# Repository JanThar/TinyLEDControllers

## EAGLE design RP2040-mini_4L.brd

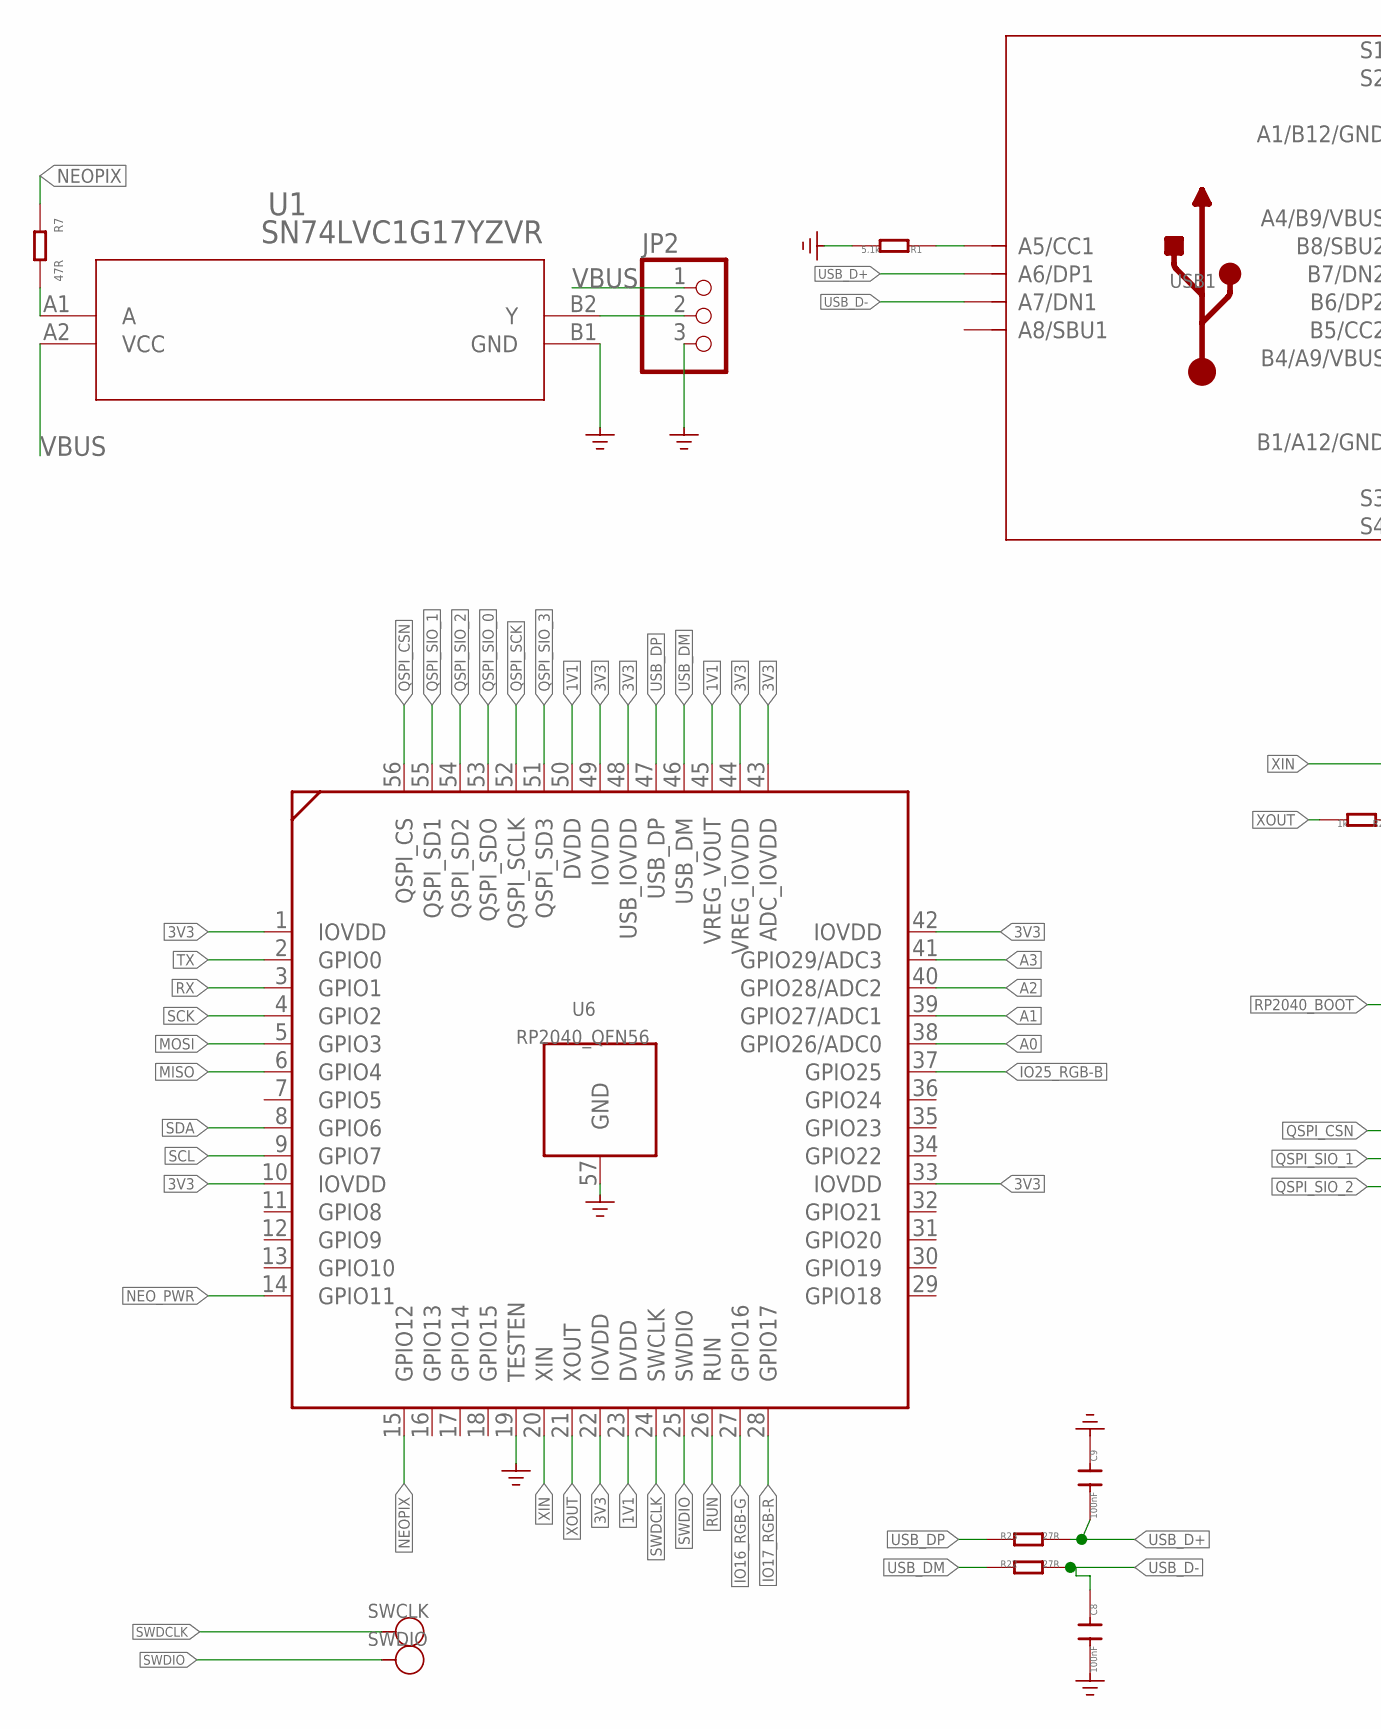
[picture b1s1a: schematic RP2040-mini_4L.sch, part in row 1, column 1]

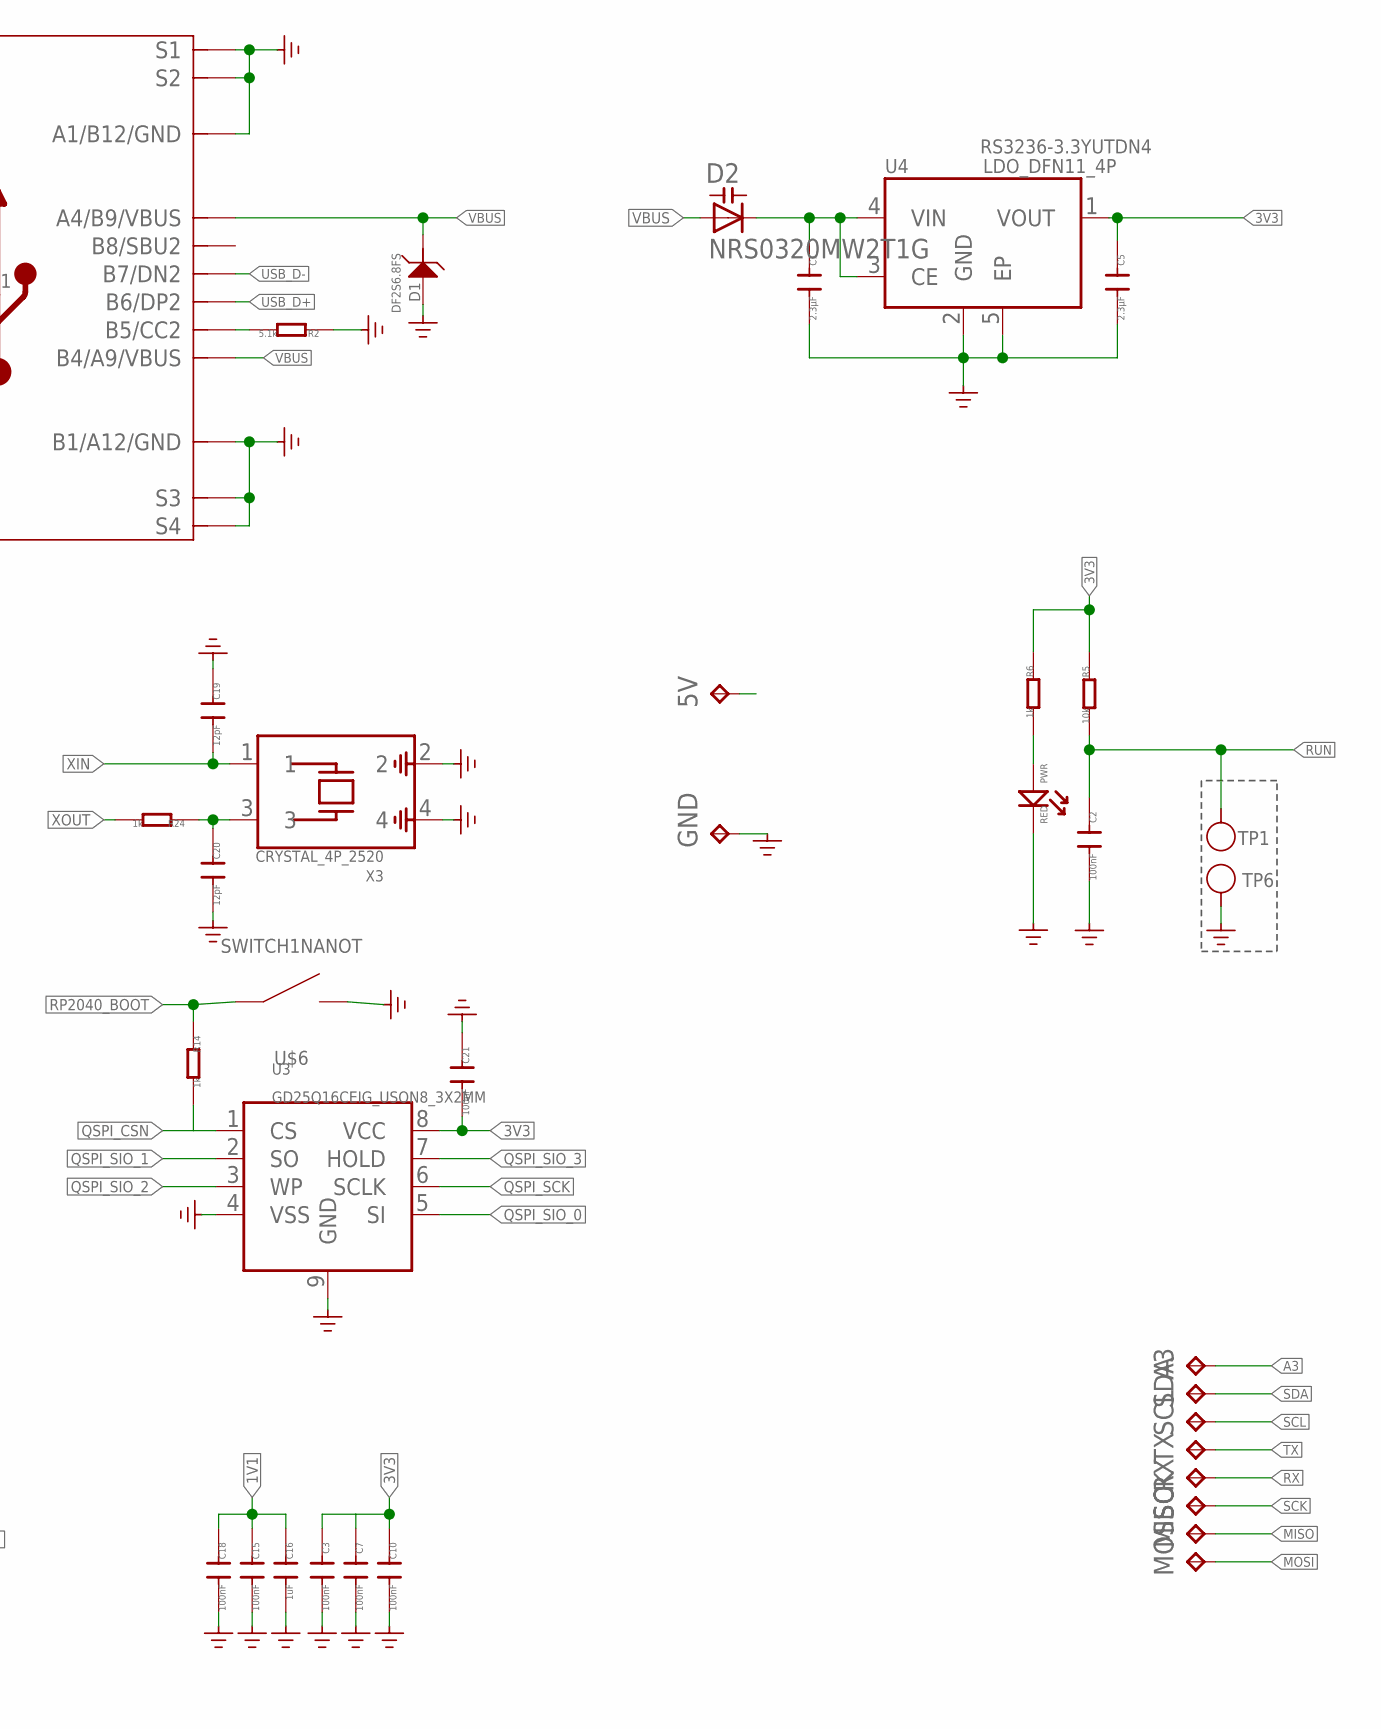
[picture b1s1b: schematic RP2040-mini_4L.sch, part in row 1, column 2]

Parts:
5V: TPTP09R; TP09R
A3: TPTP07R; TP07R
C1, C5: 2.3µF; 0201_NORMAL\NOSILK
C2, C3, C7, C8, C9, C10, C15, C18, C21: 100nF; 0201_NORMAL\NOSILK
C16: 1uF; 0201_NORMAL\NOSILK
C19, C20: 12pF; 0201_NORMAL\NOSILK
D1: DF2S6.8FS; SOD-923
D2: NRS0320MW2T1G; SOD523
GND: TPTP09R; TP09R
JP2: PINHD-1X3; 1X03
MISO: TPTP07R; TP07R
MOSI: TPTP07R; TP07R
PWR: RED; LED-0402
R1, R2: 5.1k; R0201
R5: 10k; R0201
R6, R14, R24: 1k; R0201
R7: 47R; R0201
R22, R23: 27R; R0201
RX: TPTP07R; TP07R
SCK: TPTP07R; TP07R
SCL: TPTP07R; TP07R
SDA: TPTP07R; TP07R
SWCLK: TEST-POINT-35; TP_3535
SWDIO: TEST-POINT-35; TP_3535
TP1, TP6: TEST-POINT-35; TP_3535
TX: TPTP07R; TP07R
U1: SN74LVC1G17YZVR; YZV4
U3: GD25Q16CEIG_USON8_3X2MM
U4: LDO_DFN11_4P; LDO_DFN1*1_4P
U6: RP2040_QFN56
U$6: SWITCH1NANOT; NANOT
USB1: USB2.0-TYPE-C
X3: CRYSTAL_4P_2520

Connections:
1V1: C15.1, C16.1, C18.1, U6.23 (DVDD), U6.45 (VREG_VOUT), U6.50 (DVDD)
3V3: C3.1, C5.1, C7.1, C10.1, C21.2, R5.1, R6.1, U3.8 (VCC), U4.1 (VOUT), U6.1 (IOVDD), U6.10 (IOVDD), U6.22 (IOVDD), U6.33 (IOVDD), U6.42 (IOVDD), U6.43 (ADC_IOVDD), U6.44 (VREG_IOVDD), U6.48 (USB_IOVDD), U6.49 (IOVDD)
A0: U6.38 (GPIO26/ADC0)
A1: U6.39 (GPIO27/ADC1)
A2: U6.40 (GPIO28/ADC2)
A3: A3.TP, U6.41 (GPIO29/ADC3)
GND: C1.2, C2.2, C3.2, C5.2, C7.2, C8.2, C9.1, C10.2, C15.2, C16.2, C18.2, C19.1, C20.2, C21.1, D1.2 (1), GND.TP, JP2.3, PWR.-, R1.2, R2.1, TP6.T, U1.B1 (GND), U3.4 (VSS), U3.9 (GND), U4.2 (GND), U4.5 (EP), U6.19 (TESTEN), U6.57 (GND), U$6.2 (B), USB1.A1_B12 (A1/B12/GND), USB1.B1_A12 (B1/A12/GND), USB1.S1, USB1.S2, USB1.S3, USB1.S4, USB1.S5 (S1), USB1.S6 (S2), X3.2, X3.4
IO16_RGB-G: U6.27 (GPIO16)
IO17_RGB-R: U6.28 (GPIO17)
IO25_RGB-B: U6.37 (GPIO25)
MISO: MISO.TP, U6.6 (GPIO4)
MOSI: MOSI.TP, U6.5 (GPIO3)
unnamed: R1.1, USB1.A5 (A5/CC1)
unnamed: R2.2, USB1.B5 (B5/CC2)
unnamed: JP2.2, U1.B2 (Y)
unnamed: R7.1, U1.A1 (A)
unnamed: C20.1, R24.1, X3.3
unnamed: PWR.+, R6.2
NEOPIX: R7.2, U6.15 (GPIO12)
NEO_PWR: U6.14 (GPIO11)
QSPI_CSN: R14.2, U3.1 (CS), U6.56 (QSPI_CS)
QSPI_SCK: U3.6 (SCLK), U6.52 (QSPI_SCLK)
QSPI_SIO_0: U3.5 (SI), U6.53 (QSPI_SDO)
QSPI_SIO_1: U3.2 (SO), U6.55 (QSPI_SD1)
QSPI_SIO_2: U3.3 (WP), U6.54 (QSPI_SD2)
QSPI_SIO_3: U3.7 (HOLD), U6.51 (QSPI_SD3)
RP2040_BOOT: R14.1, U$6.1 (A)
RUN: C2.1, R5.2, TP1.T, U6.26 (RUN)
RX: RX.TP, U6.3 (GPIO1)
SCK: SCK.TP, U6.4 (GPIO2)
SCL: SCL.TP, U6.9 (GPIO7)
SDA: SDA.TP, U6.8 (GPIO6)
SWDCLK: SWCLK.T, U6.24 (SWCLK)
SWDIO: SWDIO.T, U6.25 (SWDIO)
TX: TX.TP, U6.2 (GPIO0)
USB_D+: C9.2, R23.2, USB1.A6 (A6/DP1), USB1.B6 (B6/DP2)
USB_D-: C8.1, R22.2, USB1.A7 (A7/DN1), USB1.B7 (B7/DN2)
USB_DM: R22.1, U6.46 (USB_DM)
USB_DP: R23.1, U6.47 (USB_DP)
VBUS: 5V.TP, D1.1 (2), D2.A, JP2.1, U1.A2 (VCC), USB1.A4_B9 (A4/B9/VBUS), USB1.B4_A9 (B4/A9/VBUS)
VIN: C1.1, D2.C, U4.3 (CE), U4.4 (VIN)
XIN: C19.2, U6.20 (XIN), X3.1
XOUT: R24.2, U6.21 (XOUT)

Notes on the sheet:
RS3236-3.3YUTDN4

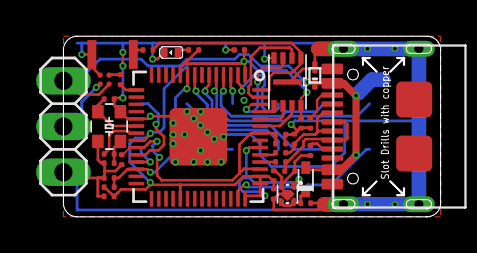
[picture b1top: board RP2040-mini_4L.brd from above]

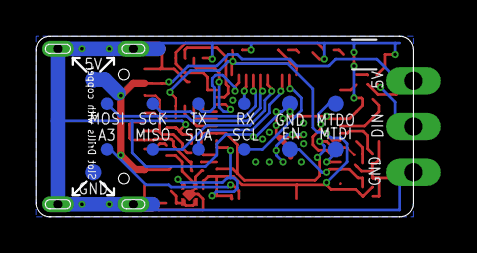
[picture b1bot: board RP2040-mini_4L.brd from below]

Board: 2 copper layers, 20.9 x 9.9 mm, 48 parts (14 on the bottom side), 36 nets.

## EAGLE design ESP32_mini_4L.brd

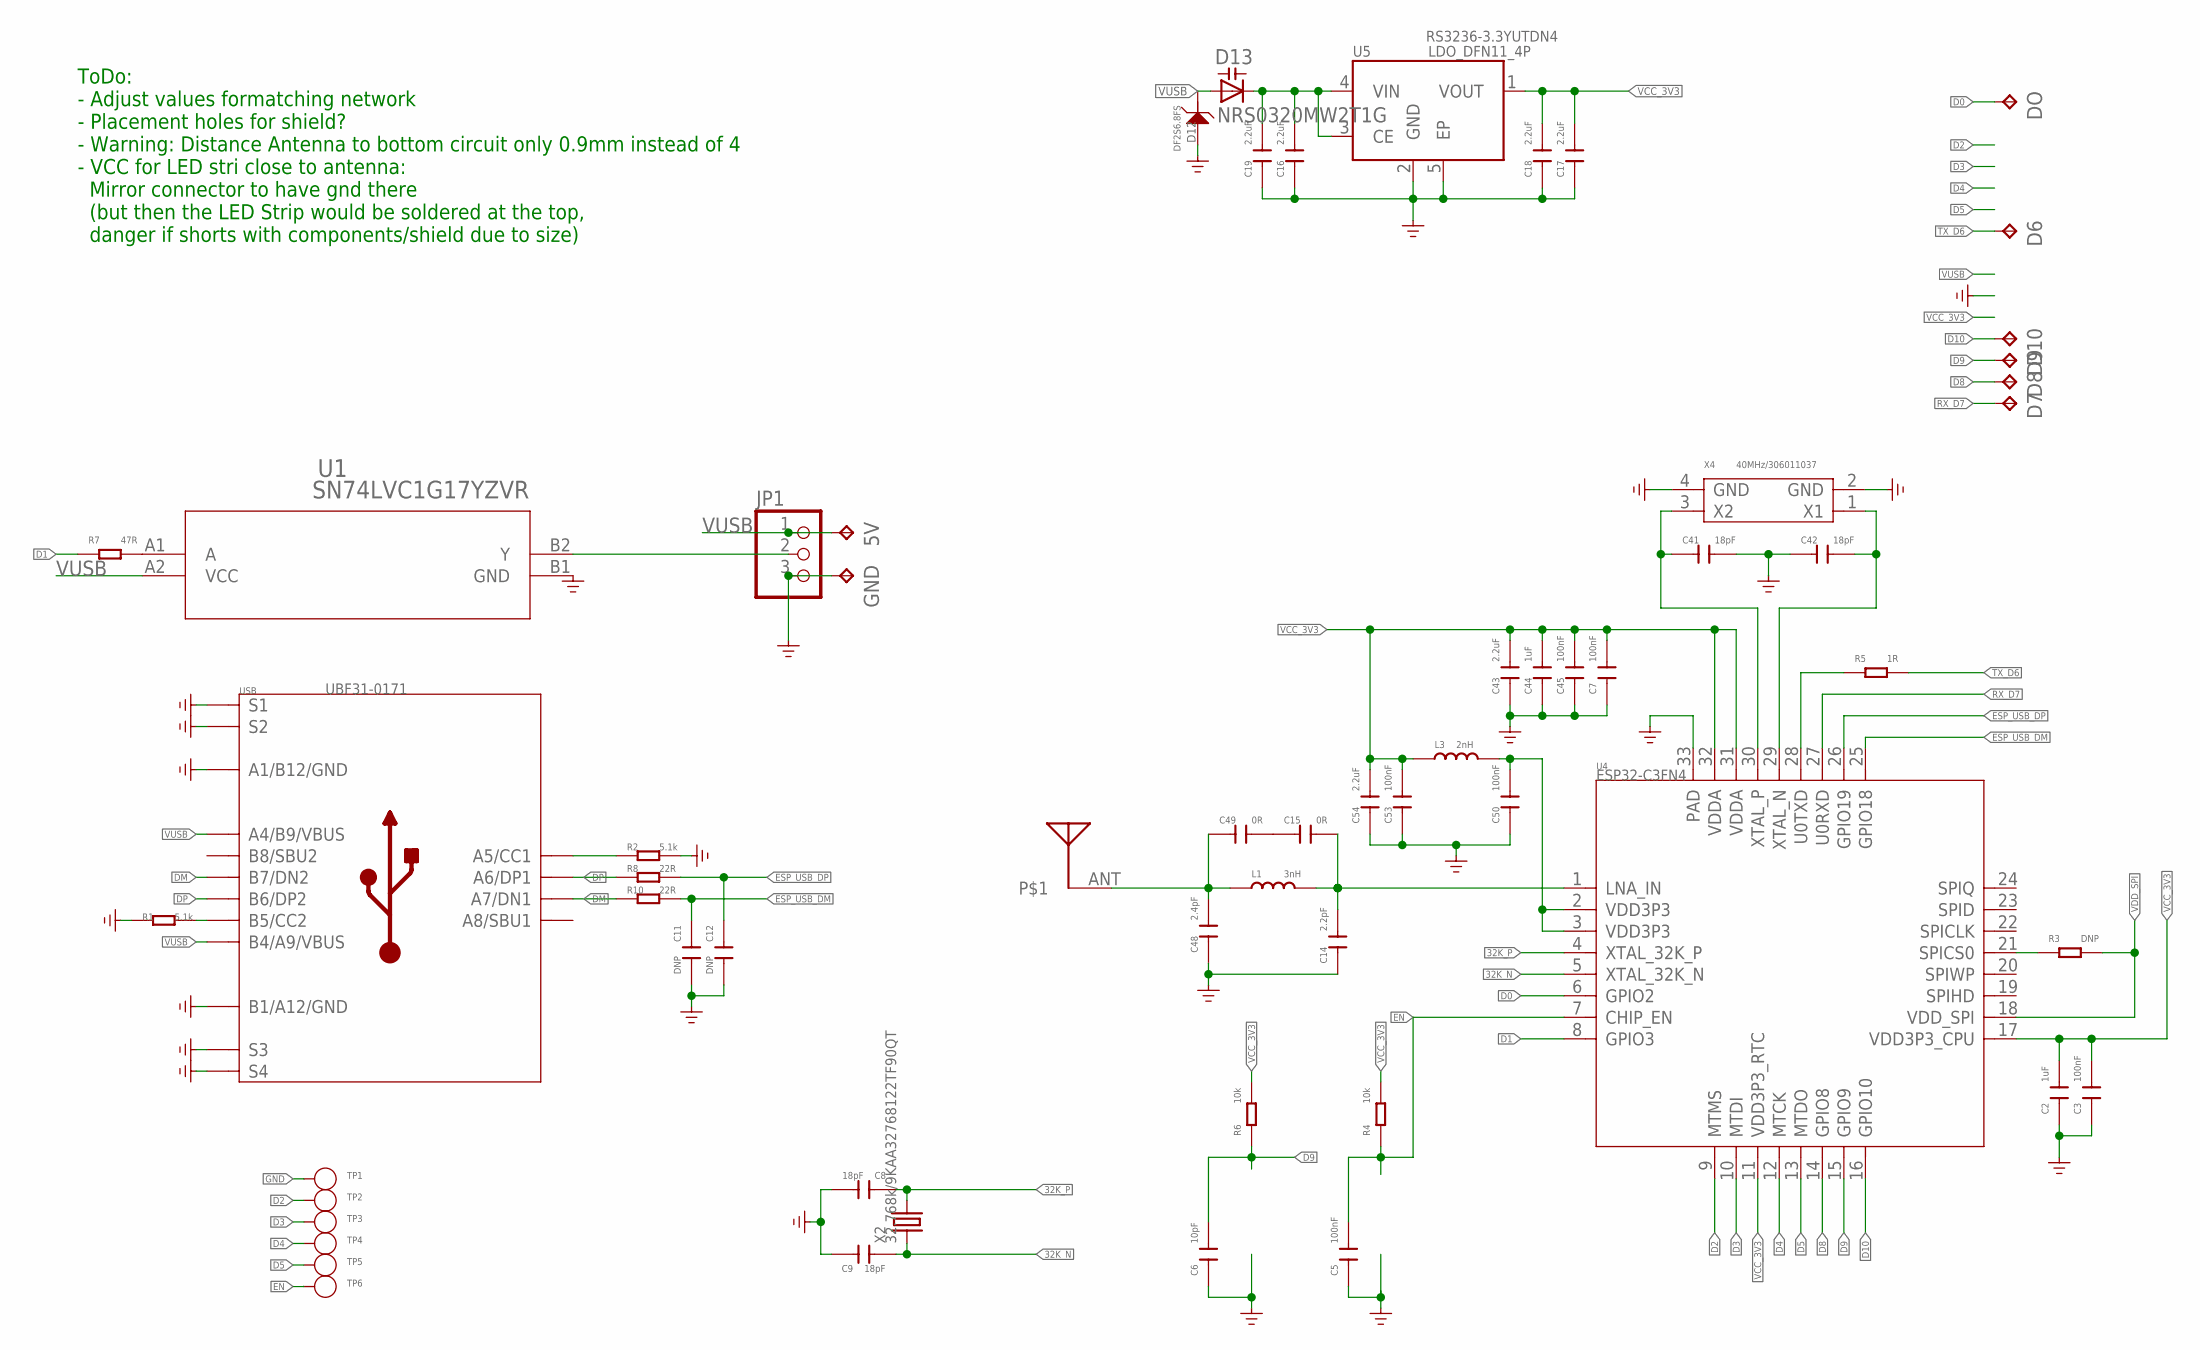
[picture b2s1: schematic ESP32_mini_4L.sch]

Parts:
5V: TPTP07R; TP07R
C2, C44: 1uF; C0201
C3, C5, C7, C45, C50, C53: 100nF; C0201
C6: 10pF; C0201
C8, C9, C41, C42: 18pF; C0201
C11, C12: DNP; C0201
C14: 2.2pF; C0201
C15, C49: 0R; C0201
C16, C17, C18, C19, C43, C54: 2.2uF; C0201
C48: 2.4pF; C0201
D6, D7, D8, D9, D10: TPTP07R; TP07R
D12: DF2S6.8FS; SOD-923
D13: NRS0320MW2T1G; SOD523
DO: TPTP09R; TP09R
GND: TPTP07R; TP07R
JP1: PINHD-1X3; 1X03
L1: 3nH; L0201
L3: 2nH; L0201
R1, R2: 5.1k; R0201
R3: DNP; R0201
R4, R6: 10k; R0201
R5: 1R; R0201
R7: 47R; R0201
R8, R10: 22R; R0201
TP1, TP2, TP3, TP4, TP5, TP6: DNP; TP_3535
U1: SN74LVC1G17YZVR; YZV4
U4: ESP32-C3FN4; QFN32G-0.5-5X5MM
U5: LDO_DFN11_4P; LDO_DFN1*1_4P
U$1: KH5220-A36KH5220-A36; KH5220-A36
USB: UBF31-0171; USB2.0-TYPE-C
X2: 32.768k/9KAA32768122TF90QT; X2-SMD-1.6X1.0X0.5MM
X4: 40MHz/306011037; X4-SMD-2.0X1.6X0.5MM

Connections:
32K_N: C9.1, U4.5 (XTAL_32K_N), X2.1
32K_P: C8.1, U4.4 (XTAL_32K_P), X2.2
D0: DO.TP, U4.6 (GPIO2)
D1: R7.2, U4.8 (GPIO3)
D2: TP2.T, U4.9 (MTMS)
D3: TP3.T, U4.10 (MTDI)
D4: TP4.T, U4.12 (MTCK)
D5: TP5.T, U4.13 (MTDO)
D8: D8.TP, U4.14 (GPIO8)
D9: C6.2, D9.TP, R6.1, U4.15 (GPIO9)
D10: D10.TP, U4.16 (GPIO10)
DM: R10.1, USB.A7 (A7/DN1), USB.B7 (B7/DN2)
DP: R8.1, USB.A6 (A6/DP1), USB.B6 (B6/DP2)
EN: C5.2, R4.1, TP6.T, U4.7 (CHIP_EN)
ESP_USB_DM: C11.2, R10.2, U4.25 (GPIO18)
ESP_USB_DP: C12.2, R8.2, U4.26 (GPIO19)
GND: C2.1, C3.1, C5.1, C6.1, C7.1, C8.2, C9.2, C11.1, C12.1, C14.1, C16.1, C17.1, C18.1, C19.1, C41.2, C42.2, C43.1, C44.1, C45.1, C48.1, C50.1, C53.1, C54.1, D12.2 (1), GND.TP, JP1.3, R1.1, R2.2, TP1.T, U1.B1 (GND), U4.33 (PAD), U5.2 (GND), U5.5 (EP), USB.A1_B12 (A1/B12/GND), USB.B1_A12 (B1/A12/GND), USB.S1, USB.S2, USB.S3, USB.S4, USB.S5 (S1), USB.S6 (S2), X4.2 (GND), X4.4 (GND)
unnamed: R2.1, USB.A5 (A5/CC1)
unnamed: R1.2, USB.B5 (B5/CC2)
unnamed: R3.1, U4.21 (SPICS0)
unnamed: JP1.2, U1.B2 (Y)
unnamed: C15.2, C49.1
unnamed: R7.1, U1.A1 (A)
unnamed: C14.2, C15.1, L1.2, U4.1 (LNA_IN)
unnamed: C41.1, U4.30 (XTAL_P), X4.3 (X2)
unnamed: C42.1, U4.29 (XTAL_N), X4.1 (X1)
unnamed: C48.2, C49.2, L1.1, U$1.ANT
unnamed: R5.2, U4.28 (U0TXD)
unnamed: C50.2, L3.2, U4.2 (VDD3P3), U4.3 (VDD3P3)
RX_D7: D7.TP, U4.27 (U0RXD)
TX_D6: D6.TP, R5.1
VCC_3V3: C2.2, C3.2, C7.2, C17.2, C18.2, C43.2, C44.2, C45.2, C53.2, C54.2, L3.1, R4.2, R6.2, U4.11 (VDD3P3_RTC), U4.17 (VDD3P3_CPU), U4.31 (VDDA), U4.32 (VDDA), U5.1 (VOUT)
VDD_SPI: R3.2, U4.18 (VDD_SPI)
VIN: C16.2, C19.2, D13.C, U5.3 (CE), U5.4 (VIN)
VUSB: 5V.TP, D12.1 (2), D13.A, JP1.1, U1.A2 (VCC), USB.A4_B9 (A4/B9/VBUS), USB.B4_A9 (B4/A9/VBUS)

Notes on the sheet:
RS3236-3.3YUTDN4
ToDo: - Adjust values formatching network - Placement holes for shield? - Warning: Distance Antenna to bottom circuit only 0.9mm instead of 4 - VCC for LED stri close to antenna: Mirror connector to have gnd there (but then the LED Strip would be soldered at the top, danger if shorts with component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

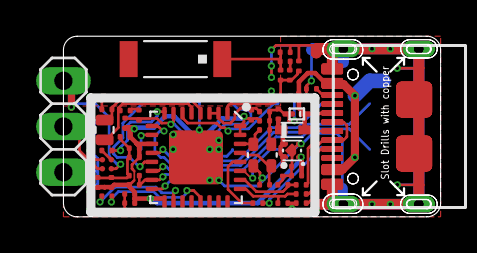
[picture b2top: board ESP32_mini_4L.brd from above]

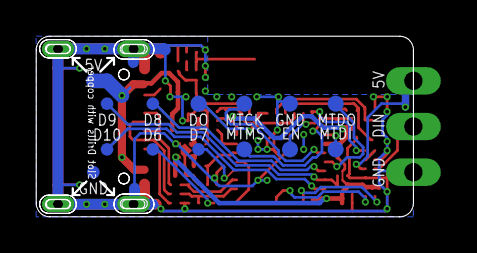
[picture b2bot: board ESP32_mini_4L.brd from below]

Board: 2 copper layers, 20.9 x 9.9 mm, 61 parts (14 on the bottom side), 35 nets.

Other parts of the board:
USB1: USB-C_USB2.0-TYPE-C

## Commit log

2024-06-02 Change to 4 layer pcb, (ESP32: adjust 5V trace)

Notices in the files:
parts and their libraries:
COPYRIGHT: Copyright (C) 2024 Ultra Librarian. All rights reserved.
